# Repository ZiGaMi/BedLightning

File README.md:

# BedLightning

Simple controller for LED strip with single rotary encoder for adjusting brightness of LED. System is desing for two LED strips with two controll switches. It's also support roommate control, where roommate can turn on/off yours LED strip and vice versa.

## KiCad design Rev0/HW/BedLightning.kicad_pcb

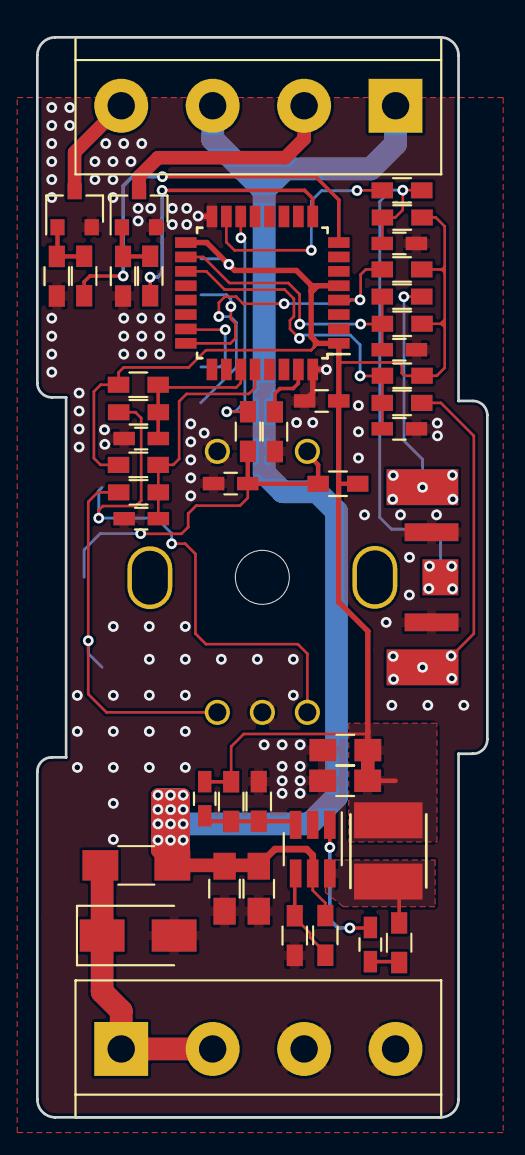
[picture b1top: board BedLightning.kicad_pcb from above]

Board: 2 copper layers, 25.0 x 60.0 mm, 47 parts (1 on the bottom side), 27 nets.

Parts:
C1: DNS; C_0603_HandSoldering
C2, C3, C4, C14: 100n; C_0603_HandSoldering
C6, C7: 10u; C_0805_HandSoldering
C8, C11: 4u7; C_0805_HandSoldering
C9, C10, C12, C13: 1n; C_0603_HandSoldering
D1: SMAJ12; D_SMA
F1: 1A; R_1206_HandSoldering
J1, J3: Conn_01x04; TerminalBlock_bornier-4_P5.08mm
J4: Conn_01x01; MountingHole_3mm
L1: 10u; Coil_1616
Q1, Q2: Q_NMOS_GSD; SOT-23
R1: 22k; R_0603_HandSoldering
R2: 6k8; R_0603_HandSoldering
R3, R6, R12, R13, R18, R19: 1k; R_0603_HandSoldering
R4, R9, R10, R11, R16, R17: DNS; R_0603_HandSoldering
R5: 10R; R_0603_HandSoldering
R7: 56k; R_0603_HandSoldering
R8, R14, R15: 10k; R_0603_HandSoldering
R20, R21: 100R; R_0603_HandSoldering
R22, R23: 100k; R_0603_HandSoldering
SW1: Rotary_Encoder_Switch; EC11E09244BS
U1: BL9341; SOT-23-6_Handsoldering
U2: STM32F031K6Tx; LQFP-32_7x7mm_Pitch0.8mm

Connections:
+3V3: C1.2, C6.2, C7.2, C14.1, L1.2, R1.1, R4.2, R9.2, R10.2, R11.2, R14.1, R16.2, R17.2, U2.1, U2.5, U2.17
+12P: C8.2, C11.2, F1.2, J1.1, J1.3, R7.1, U1.5
+12V: D1.1, F1.1, J3.1, J3.2
/BTN1: C2.2, R3.1, R4.1, SW1.S1
/BTN1_F: R3.2, U2.14
/BTN2: C4.2, R6.1, R9.1
/BTN2_F: R6.2, U2.15
/LED1: J1.4, Q2.3
/LED1_GATE: R21.2, U2.8
/LED2: J1.2, Q1.3
/LED2_GATE: R20.2, U2.9
/NRST: R14.2, U2.4
/RE1_A: R12.1, SW1.A
/RE1_A_F: C10.2, R11.1, R12.2, U2.27
/RE1_B: R13.1, SW1.B
/RE1_B_F: C9.2, R10.1, R13.2, U2.28
/RE2_A_F: C13.2, R17.1, R18.2, U2.18
/RE2_B_F: C12.2, R16.1, R19.2, U2.19
GND: C2.1, C4.1, C6.1, C7.1, C8.1, C9.1, C10.1, C11.1, C12.1, C13.1, C14.2, D1.2, J3.3, J3.4, Q1.2, Q2.2, R2.2, R8.2, R15.2, R22.2, R23.2, SW1.C, SW1.S2, U1.2, U2.16, U2.32
unnamed: C1.1, R1.2, R2.1, U1.3
unnamed: C3.1, R5.2
unnamed: C3.2, U1.1
unnamed: L1.1, R5.1, U1.6
unnamed: Q1.1, R20.1, R22.1
unnamed: Q2.1, R21.1, R23.1
unnamed: R7.2, R8.1, U1.4
unnamed: R15.1, U2.31

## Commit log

2019-05-05 new file: Rev0/Docs/BedLightning_rev0.pdf new file: Rev0/FW/src/BedLightning.h new file: Rev0/FW/src/BedLightningDrv.c new file: Rev0/FW/src/RotaryEncoderDrv.c new file: Rev0/FW/src/RotaryEncoderDrv.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
